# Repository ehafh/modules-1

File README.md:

Schematic and PCB files for the synthesizer modules developed by [1979](https://1979.ws/)
Open Source Buchla conversions of Mutable Instruments modules.

Currently incomplete, waiting on Grayscale / 1979 updates.

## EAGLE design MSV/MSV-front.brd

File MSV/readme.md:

Overview
=======

Modal Synthesis Voice is a synthesizer module for the Buchla format, developed and manufactured by [1979](https://1979.ws/). It is based on [Elements](https://mutable-instruments.net/modules/elements/) by [Mutable Instruments](https://mutable-instruments.net/). The original source files for Elements can be found in the Mutable Instruments [Github](https://github.com/pichenettes/eurorack) repository.

Visit [1979.ws/modal-synthesis-voice](https://1979.ws/modal-synthesis-voice/) for more information.

License
=======

These schematic and PCB files are distributed under the Creative Commons [CC-BY-SA 3.0](https://creativecommons.org/licenses/by-sa/3.0/) license, the same license used by the original hardware.

CC BY-SA 3.0 does not confer the right to use intellectual property such as trademarks, brand names, and logos. 1979, Modal Synthesis Voice, Mutable Instruments, and Elements are trademarks of their respective owners and should not be used without permission.

Firmware
=======

The MSV uses the firmware from Elements with no modifications.

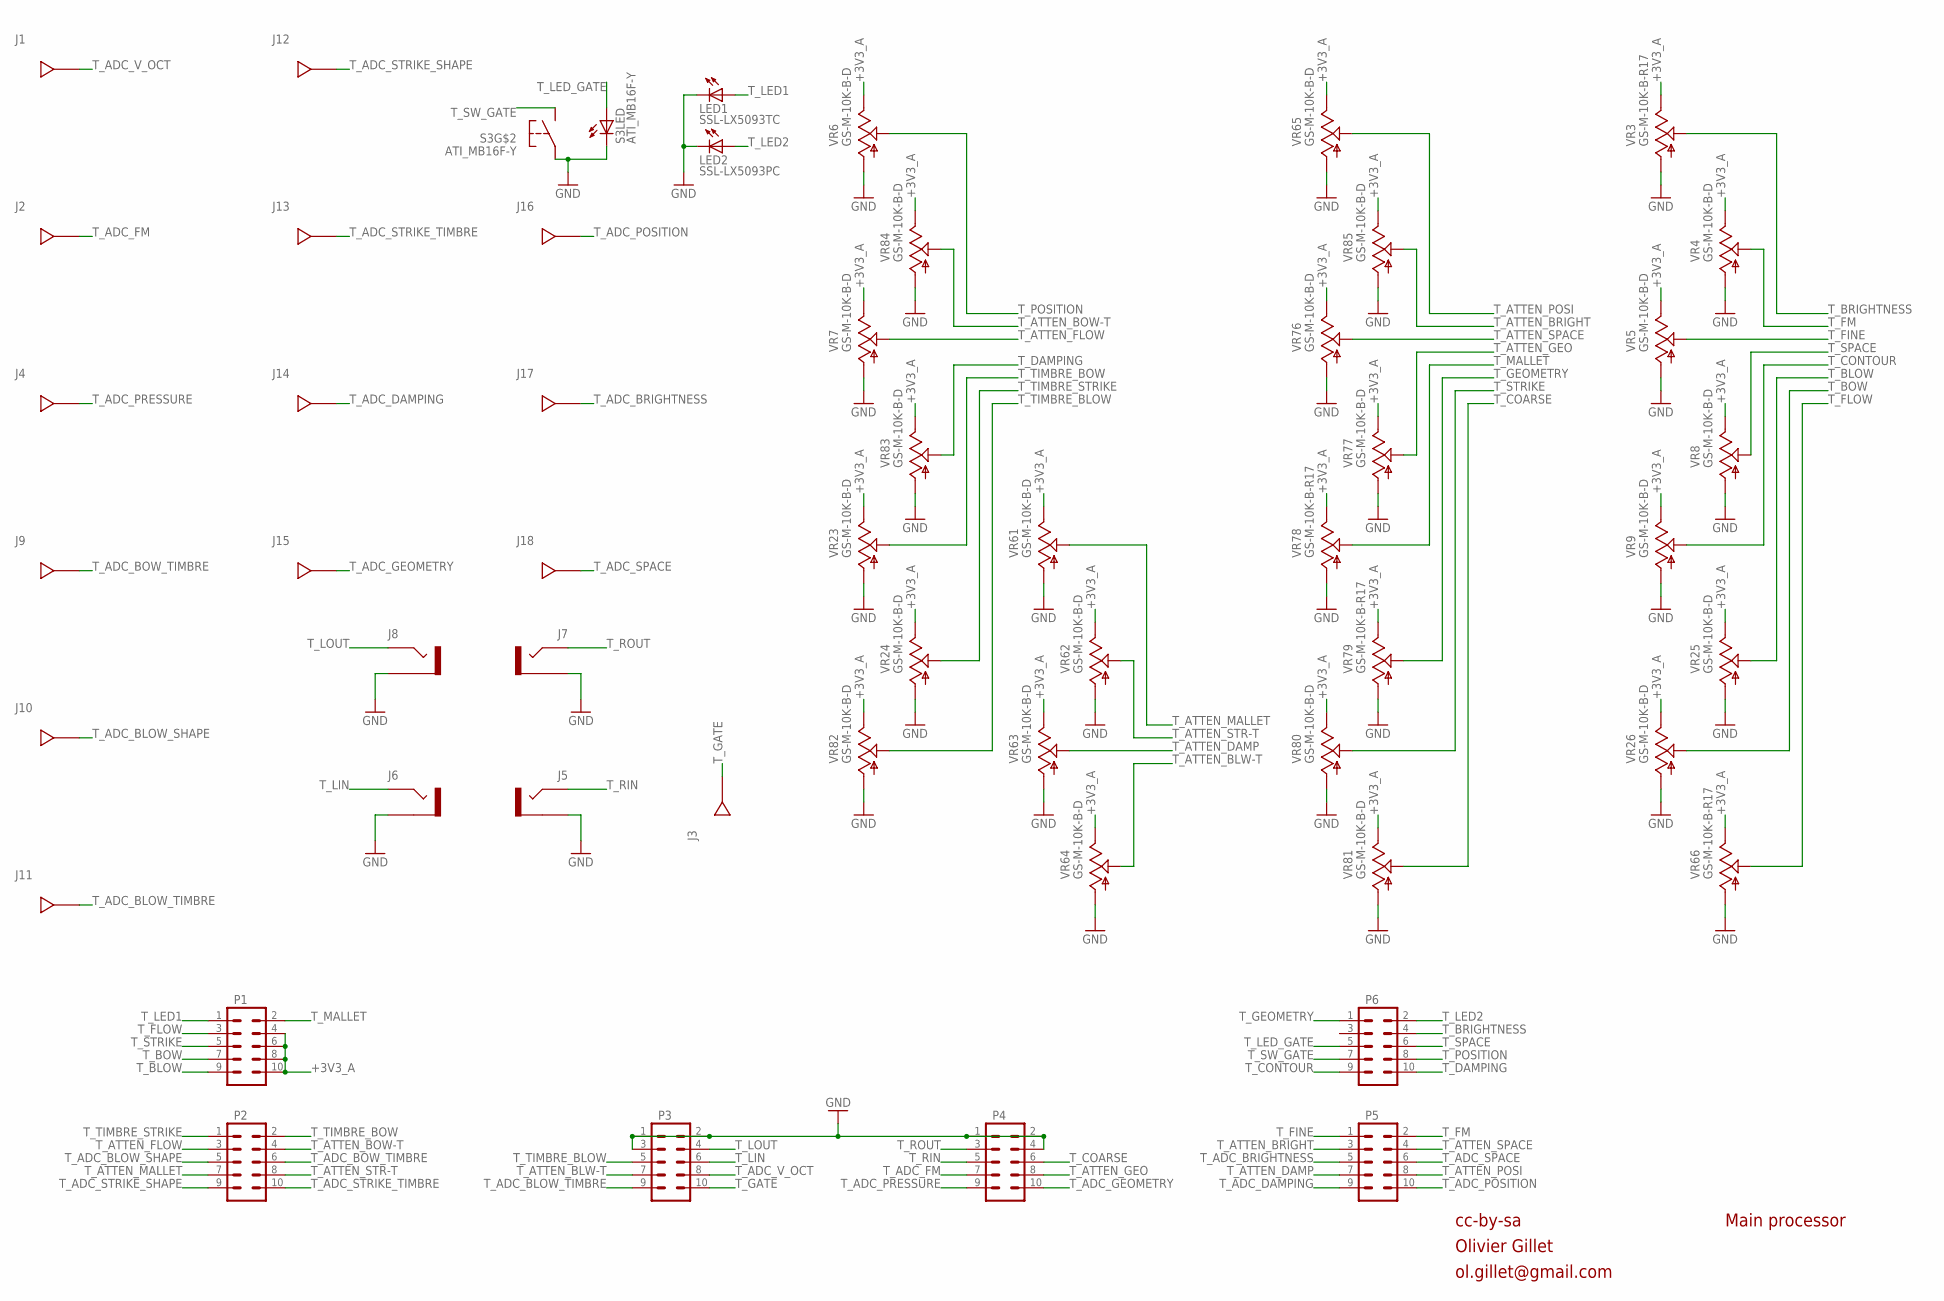
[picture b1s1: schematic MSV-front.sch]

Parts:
J1: BANANA_JACK_GRAY; JOHNSON_SILK
J2, J4, J9, J10, J11, J12, J13, J14, J15, J16, J17, J18: BANANA_JACK_BLACK; JOHNSON_SILK
J3: BANANA_JACK_ORANGE; JOHNSON_SILK
J5, J6, J7, J8: BUCHLA_AUDIO_JACK_ALT; AUDIO_ALT
LED1: SSL-LX5093TC; LED_SILK
LED2: SSL-LX5093PC; LED_SILK
P1, P2, P3, P4, P5, P6: M05X2_LOCK_FEMALE; 2X5_LOCK_FEMALE
S3: ATI_MB16F-Y; MB16F_SILK
VR3, VR66, VR78, VR79: GS-M-10K-B-R17; 9MM_SNAP-IN_POT_SILK
VR4, VR5, VR6, VR7, VR8, VR9, VR23, VR24, VR25, VR26, VR61, VR62, VR63, VR64, VR65, VR76, VR77, VR80, VR81, VR82, VR83, VR84, VR85: GS-M-10K-B-D; 9MM_SNAP-IN_POT_SILK

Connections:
+3V3_A: P1.4, P1.6, P1.8, P1.10, VR3.3, VR4.3, VR5.3, VR6.3, VR7.3, VR8.3, VR9.3, VR23.3, VR24.3, VR25.3, VR26.3, VR61.3, VR62.3, VR63.3, VR64.3, VR65.3, VR66.3, VR76.3, VR77.3, VR78.3, VR79.3, VR80.3, VR81.3, VR82.3, VR83.3, VR84.3, VR85.3
GND: J5.G (2), J6.G (2), J7.G (2), J8.G (2), LED1.K (C), LED2.K (C), P3.1, P3.2, P3.3, P4.1, P4.2, P4.4, S3.2 (1), S3.4 (L2), VR3.1, VR4.1, VR5.1, VR6.1, VR7.1, VR8.1, VR9.1, VR23.1, VR24.1, VR25.1, VR26.1, VR61.1, VR62.1, VR63.1, VR64.1, VR65.1, VR66.1, VR76.1, VR77.1, VR78.1, VR79.1, VR80.1, VR81.1, VR82.1, VR83.1, VR84.1, VR85.1
T_ADC_BLOW_SHAPE: J10.1, P2.5
T_ADC_BLOW_TIMBRE: J11.1, P3.9
T_ADC_BOW_TIMBRE: J9.1, P2.6
T_ADC_BRIGHTNESS: J17.1, P5.5
T_ADC_DAMPING: J14.1, P5.9
T_ADC_FM: J2.1, P4.7
T_ADC_GEOMETRY: J15.1, P4.10
T_ADC_POSITION: J16.1, P5.10
T_ADC_PRESSURE: J4.1, P4.9
T_ADC_SPACE: J18.1, P5.6
T_ADC_STRIKE_SHAPE: J12.1, P2.9
T_ADC_STRIKE_TIMBRE: J13.1, P2.10
T_ADC_V_OCT: J1.1, P3.8
T_ATTEN_BLW-T: P3.7, VR64.2
T_ATTEN_BOW-T: P2.4, VR84.2
T_ATTEN_BRIGHT: P5.3, VR85.2
T_ATTEN_DAMP: P5.7, VR63.2
T_ATTEN_FLOW: P2.3, VR7.2
T_ATTEN_GEO: P4.8, VR77.2
T_ATTEN_MALLET: P2.7, VR61.2
T_ATTEN_POSI: P5.8, VR65.2
T_ATTEN_SPACE: P5.4, VR76.2
T_ATTEN_STR-T: P2.8, VR62.2
T_BLOW: P1.9, VR25.2
T_BOW: P1.7, VR26.2
T_BRIGHTNESS: P6.4, VR3.2
T_COARSE: P4.6, VR81.2
T_CONTOUR: P6.9, VR9.2
T_DAMPING: P6.10, VR83.2
T_FINE: P5.1, VR5.2
T_FLOW: P1.3, VR66.2
T_FM: P5.2, VR4.2
T_GATE: J3.1, P3.10
T_GEOMETRY: P6.1, VR79.2
T_LED1: LED1.A, P1.1
T_LED2: LED2.A, P6.2
T_LED_GATE: P6.5, S3.3 (L1)
T_LIN: J6.S (1), P3.6
T_LOUT: J8.S (1), P3.4
T_MALLET: P1.2, VR78.2
T_POSITION: P6.8, VR6.2
T_RIN: J5.S (1), P4.5
T_ROUT: J7.S (1), P4.3
T_SPACE: P6.6, VR8.2
T_STRIKE: P1.5, VR80.2
T_SW_GATE: P6.7, S3.1 (2)
T_TIMBRE_BLOW: P3.5, VR82.2
T_TIMBRE_BOW: P2.2, VR23.2
T_TIMBRE_STRIKE: P2.1, VR24.2

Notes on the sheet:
cc-by-sa
Olivier Gillet
ol.gillet@gmail.com
Main processor

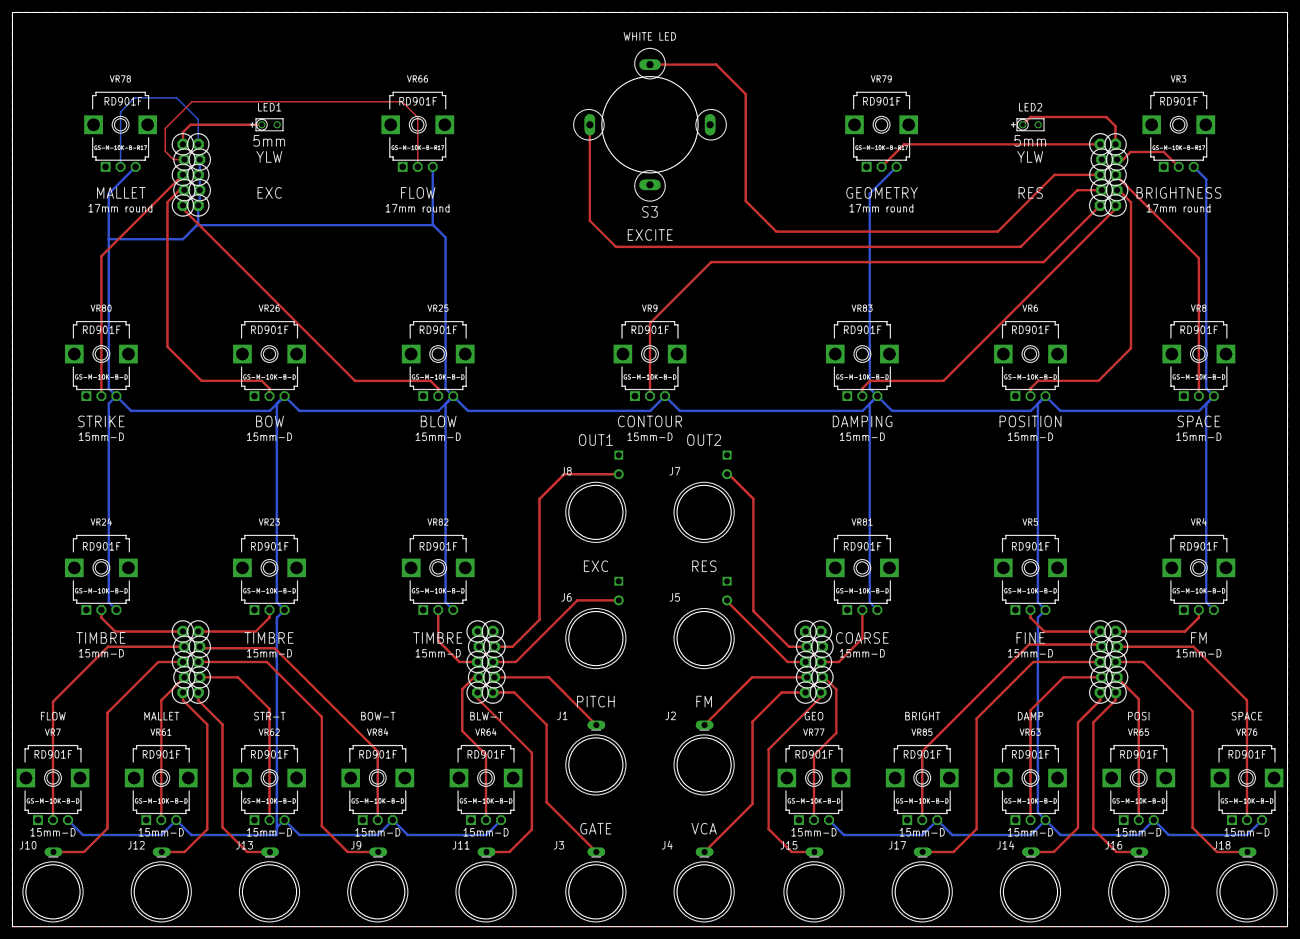
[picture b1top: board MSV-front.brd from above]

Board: 2 copper layers, 212.0 x 152.0 mm, 54 parts (1 on the bottom side), 51 nets.

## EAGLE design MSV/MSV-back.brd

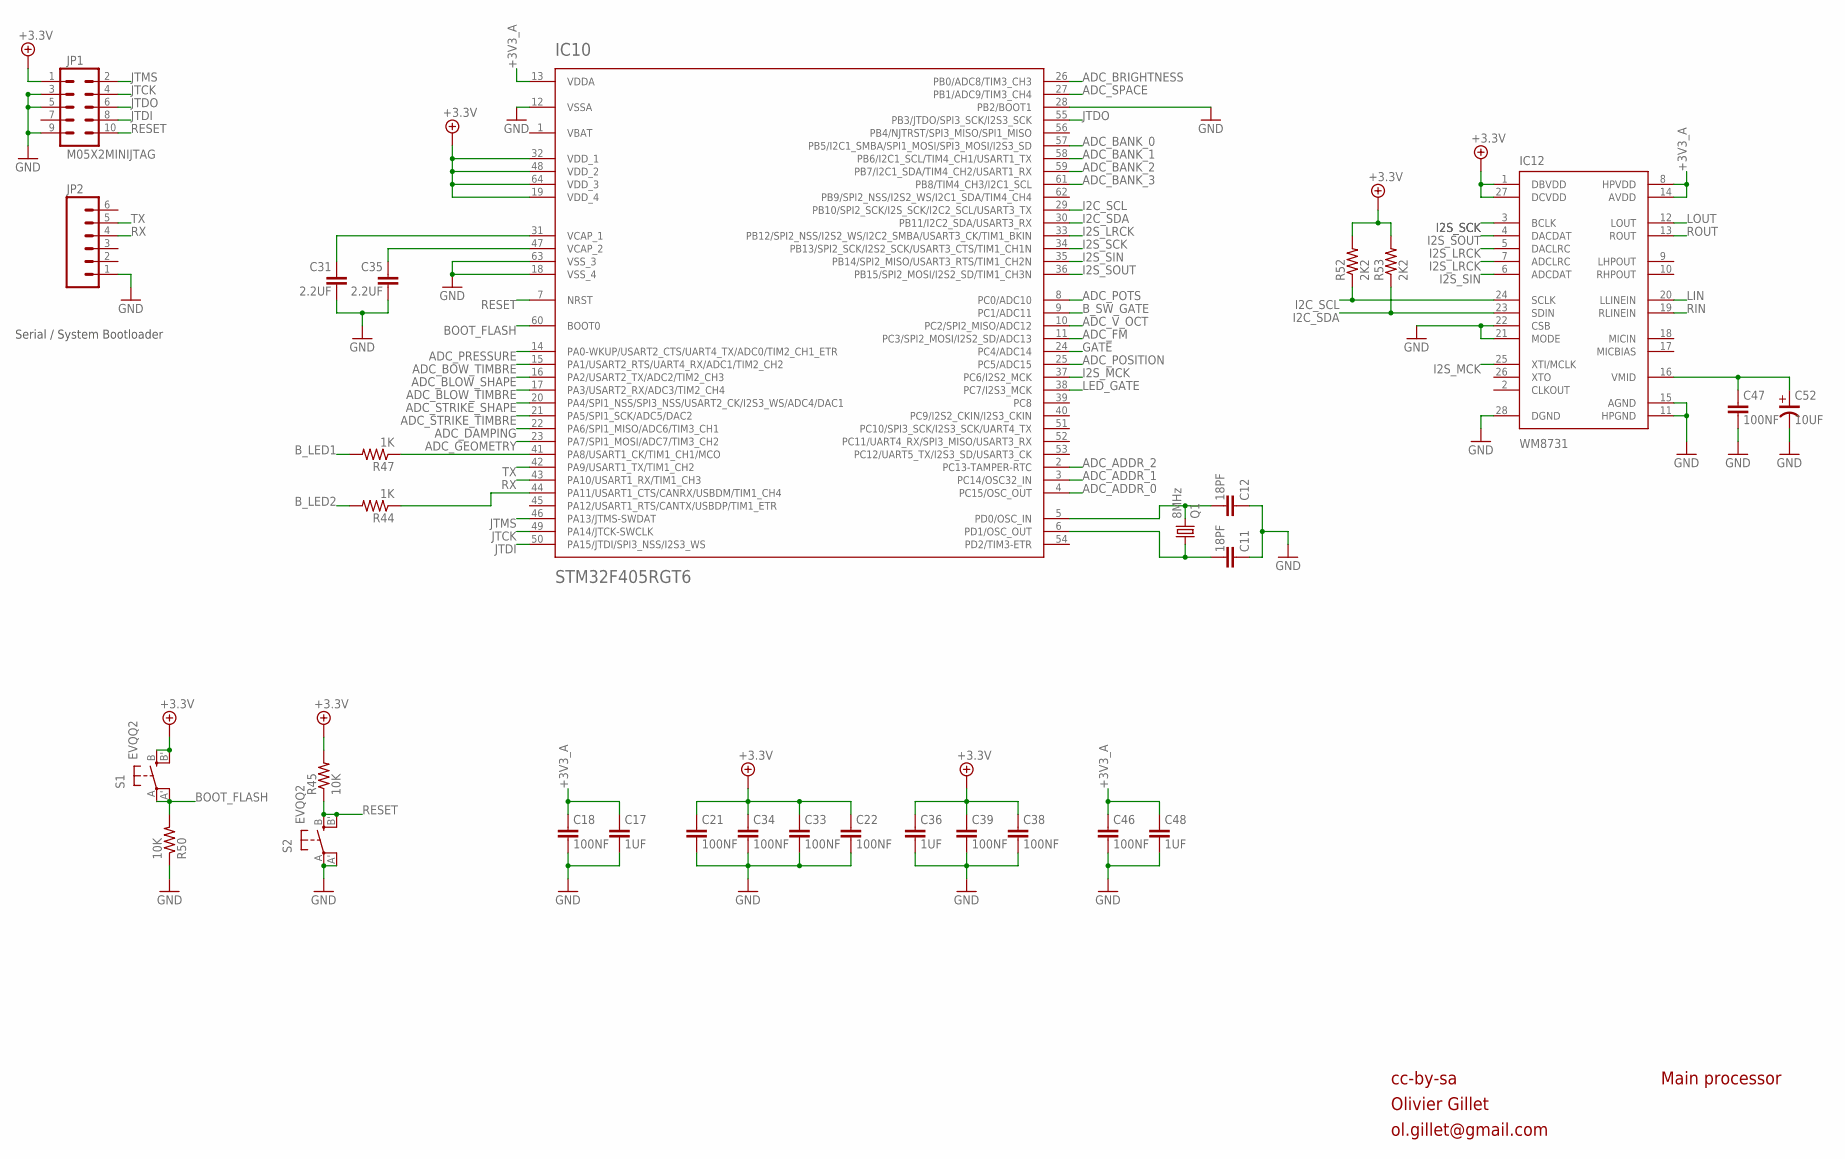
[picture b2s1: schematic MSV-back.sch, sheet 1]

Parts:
C11, C12: 18PF; C0603
C17, C36, C48: 1UF; C0603
C18, C21, C22, C33, C34, C38, C39, C46, C47: 100NF; C0603
C31, C35: 2.2UF; C0603
C52: 10UF; PANASONIC_B
IC10: STM32F405RGT6; TQFP-10X10-64
IC12: WM8731; SSOP-28
JP1: M05X2MINIJTAG; 2X5-1.27
JP2: M06_SQUARE; 1X06_SQUARE
Q1: 8MHz; HC49UP
R44, R47: 1K; R0603
R45, R50: 10K; R0603
R52, R53: 2K2; R0603
S1, S2: EVQQ2; EVQ-Q2

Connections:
+3V3_A: C17.1, C18.1, C46.1, C48.1, IC10.13 (VDDA), IC12.8 (HPVDD), IC12.14 (AVDD); also elsewhere on the board
+3V3_D: C21.1, C22.1, C33.1, C34.1, C36.1, C38.1, C39.1, IC10.19 (VDD_4), IC10.32 (VDD_1), IC10.48 (VDD_2), IC10.64 (VDD_3), IC12.1 (DBVDD), IC12.27 (DCVDD), JP1.1, R45.2, R52.2, R53.2, S1.B (S), S1.B' (S1); also elsewhere on the board
ADC_ADDR_0: IC10.4 (PC15/OSC_OUT); also elsewhere on the board
ADC_ADDR_1: IC10.3 (PC14/OSC32_IN); also elsewhere on the board
ADC_ADDR_2: IC10.2 (PC13-TAMPER-RTC); also elsewhere on the board
ADC_BANK_0: IC10.57 (PB5/I2C1_SMBA/SPI1_MOSI/SPI3_MOSI/I2S3_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); also elsewhere on the board
ADC_BANK_1: IC10.58 (PB6/I2C1_SCL/TIM4_CH1/USART1_TX); also elsewhere on the board
ADC_BANK_2: IC10.59 (PB7/I2C1_SDA/TIM4_CH2/USART1_RX); also elsewhere on the board
ADC_BANK_3: IC10.61 (PB8/TIM4_CH3/I2C1_SCL); also elsewhere on the board
ADC_BLOW_SHAPE: IC10.16 (PA2/USART2_TX/ADC2/TIM2_CH3); also elsewhere on the board
ADC_BLOW_TIMBRE: IC10.17 (PA3/USART2_RX/ADC3/TIM2_CH4); also elsewhere on the board
ADC_BOW_TIMBRE: IC10.15 (PA1/USART2_RTS/UART4_RX/ADC1/TIM2_CH2); also elsewhere on the board
ADC_BRIGHTNESS: IC10.26 (PB0/ADC8/TIM3_CH3); also elsewhere on the board
ADC_DAMPING: IC10.22 (PA6/SPI1_MISO/ADC6/TIM3_CH1); also elsewhere on the board
ADC_FM: IC10.11 (PC3/SPI2_MOSI/I2S2_SD/ADC13); also elsewhere on the board
ADC_GEOMETRY: IC10.23 (PA7/SPI1_MOSI/ADC7/TIM3_CH2); also elsewhere on the board
ADC_POSITION: IC10.25 (PC5/ADC15); also elsewhere on the board
ADC_POTS: IC10.8 (PC0/ADC10); also elsewhere on the board
ADC_PRESSURE: IC10.14 (PA0-WKUP/USART2_CTS/UART4_TX/ADC0/TIM2_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); also elsewhere on the board
ADC_SPACE: IC10.27 (PB1/ADC9/TIM3_CH4); also elsewhere on the board
ADC_STRIKE_SHAPE: IC10.20 (PA4/SPI1_NSS/SPI3_NSS/USART2_CK/I2S3_WS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); also elsewhere on the board
ADC_STRIKE_TIMBRE: IC10.21 (PA5/SPI1_SCK/ADC5/DAC2); also elsewhere on the board
ADC_V_OCT: IC10.10 (PC2/SPI2_MISO/ADC12); also elsewhere on the board
BOOT_FLASH: IC10.60 (BOOT0), R50.2, S1.A, S1.A' (P1)
B_LED1: R47.2; also elsewhere on the board
B_LED2: R44.2; also elsewhere on the board
B_SW_GATE: IC10.9 (PC1/ADC11); also elsewhere on the board
GATE: IC10.24 (PC4/ADC14); also elsewhere on the board
GND: C11.1, C12.1, C17.2, C18.2, C21.2, C22.2, C31.2, C33.2, C34.2, C35.2, C36.2, C38.2, C39.2, C46.2, C47.2, C48.2, C52.- (NEG), IC10.12 (VSSA), IC10.18 (VSS_4), IC10.28 (PB2/BOOT1), IC10.63 (VSS_3), IC12.11 (HPGND), IC12.15 (AGND), IC12.21 (MODE), IC12.22 (CSB), IC12.28 (DGND), JP1.3, JP1.5, JP1.9, JP2.1, R50.1, S2.A, S2.A' (P1); also elsewhere on the board
I2C_SCL: IC10.29 (PB10/SPI2_SCK/I2S_SCK/I2C2_SCL/USART3_TX), IC12.24 (SCLK), R52.1
I2C_SDA: IC10.30 (PB11/I2C2_SDA/USART3_RX), IC12.23 (SDIN), R53.1
I2S_LRCK: IC10.33 (PB12/SPI2_NSS/I2S2_WS/I2C2_SMBA/USART3_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), IC12.5 (DACLRC), IC12.7 (ADCLRC)
I2S_MCK: IC10.37 (PC6/I2S2_MCK), IC12.25 (XTI/MCLK)
I2S_SCK: IC10.34 (PB13/SPI2_SCK/I2S2_SCK/USART3_CTS/TIM1_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), IC12.3 (BCLK)
I2S_SIN: IC10.35 (PB14/SPI2_MISO/USART3_RTS/TIM1_CH2N), IC12.6 (ADCDAT)
I2S_SOUT: IC10.36 (PB15/SPI2_MOSI/I2S2_SD/TIM1_CH3N), IC12.4 (DACDAT)
JTCK: IC10.49 (PA14/JTCK-SWCLK), JP1.4
JTDI: IC10.50 (PA15/JTDI/SPI3_NSS/I2S3_WS), JP1.8
JTDO: IC10.55 (PB3/JTDO/SPI3_SCK/I2S3_SCK), JP1.6
JTMS: IC10.46 (PA13/JTMS-SWDAT), JP1.2
LED_GATE: IC10.38 (PC7/I2S3_MCK); also elsewhere on the board
LIN: IC12.20 (LLINEIN); also elsewhere on the board
LOUT: IC12.12 (LOUT); also elsewhere on the board
unnamed: C12.2, IC10.5 (PD0/OSC_IN), Q1.2
unnamed: C11.2, IC10.6 (PD1/OSC_OUT), Q1.1
unnamed: C35.1, IC10.47 (VCAP_2)
unnamed: C47.1, C52.+ (POS), IC12.16 (VMID)
unnamed: C31.1, IC10.31 (VCAP_1)
unnamed: IC10.44 (PA11/USART1_CTS/CANRX/USBDM/TIM1_CH4), R44.1
unnamed: IC10.41 (PA8/USART1_CK/TIM1_CH1/MCO), R47.1
RESET: IC10.7 (NRST), JP1.10, R45.1, S2.B (S), S2.B' (S1)
RIN: IC12.19 (RLINEIN); also elsewhere on the board
ROUT: IC12.13 (ROUT); also elsewhere on the board
RX: IC10.43 (PA10/USART1_RX/TIM1_CH3), JP2.4
TX: IC10.42 (PA9/USART1_TX/TIM1_CH2), JP2.5
VBAT: IC10.1 (VBAT)

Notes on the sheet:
cc-by-sa
Olivier Gillet
ol.gillet@gmail.com
Main processor
Serial / System Bootloader

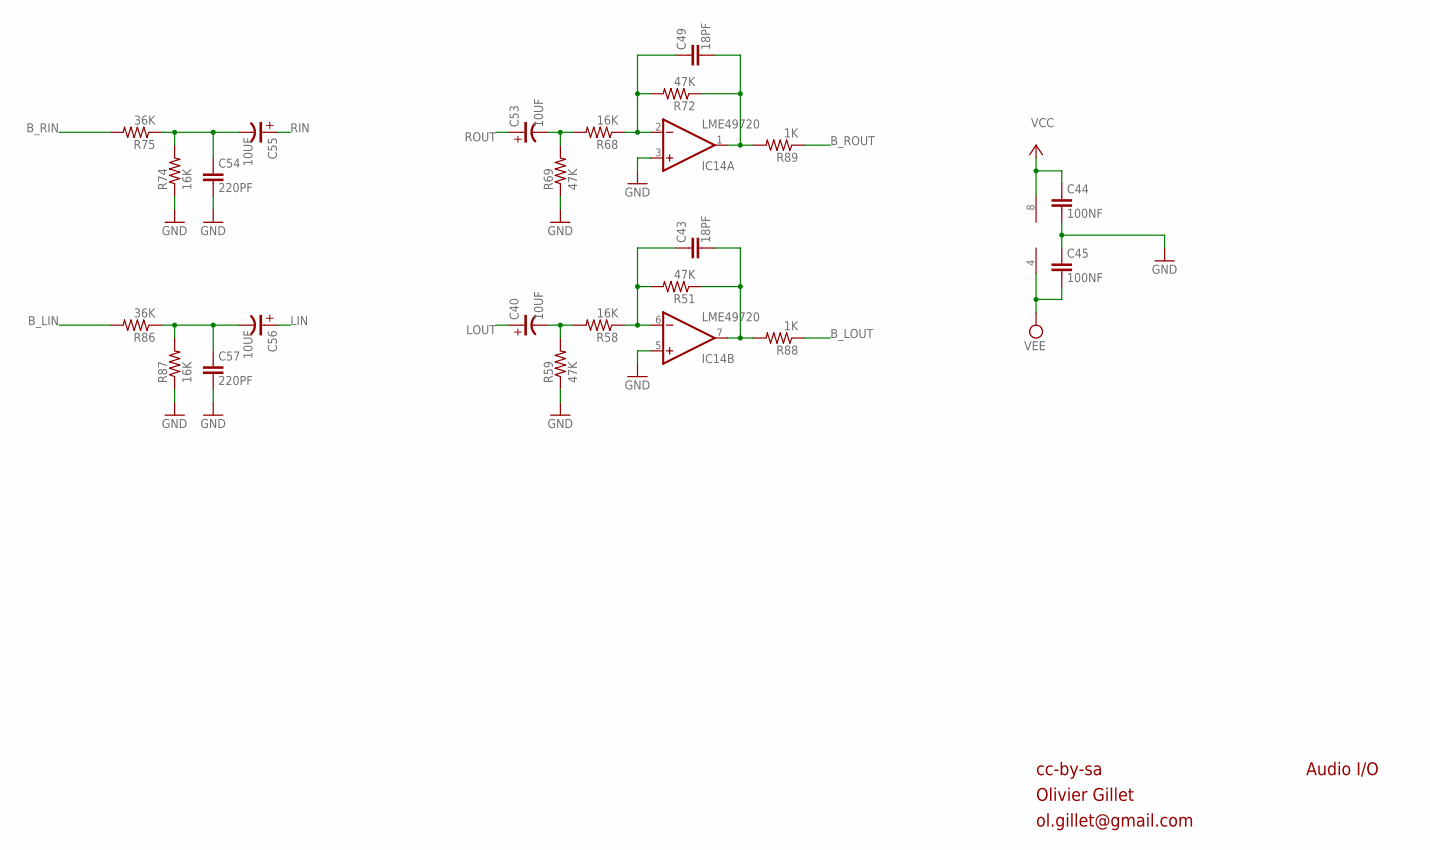
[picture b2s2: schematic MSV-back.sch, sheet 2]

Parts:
C40, C53, C55, C56: 10UF; PANASONIC_B
C43, C49: 18PF; C0603
C44, C45: 100NF; C0603
C54, C57: 220PF; C0603
IC14: LME49720; TSSOP-8
R51, R59, R69, R72: 47K; R0603
R58, R68, R74, R87: 16K; R0603
R75, R86: 36K; R0603
R88, R89: 1K; R0603

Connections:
B_LIN: R86.2; also elsewhere on the board
B_LOUT: R88.1; also elsewhere on the board
B_RIN: R75.2; also elsewhere on the board
B_ROUT: R89.1; also elsewhere on the board
GND: C44.2, C45.1, C54.2, C57.2, IC14.3 (+IN), IC14.5 (+IN), R59.1, R69.1, R74.1, R87.1; also elsewhere on the board
LIN: C56.+ (POS); also elsewhere on the board
LOUT: C40.+ (POS); also elsewhere on the board
unnamed: C56.- (NEG), C57.1, R86.1, R87.2
unnamed: C54.1, C55.- (NEG), R74.2, R75.1
unnamed: C40.- (NEG), R58.2, R59.2
unnamed: C43.1, IC14.6 (-IN), R51.2, R58.1
unnamed: C43.2, IC14.7 (OUT), R51.1, R88.2
unnamed: C53.- (NEG), R68.2, R69.2
unnamed: C49.1, IC14.2 (-IN), R68.1, R72.2
unnamed: C49.2, IC14.1 (OUT), R72.1, R89.2
RIN: C55.+ (POS); also elsewhere on the board
ROUT: C53.+ (POS); also elsewhere on the board
VCC: C44.1, IC14.8 (V+); also elsewhere on the board
VEE: C45.2, IC14.4 (V-); also elsewhere on the board

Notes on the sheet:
cc-by-sa
Olivier Gillet
ol.gillet@gmail.com
Audio I/O

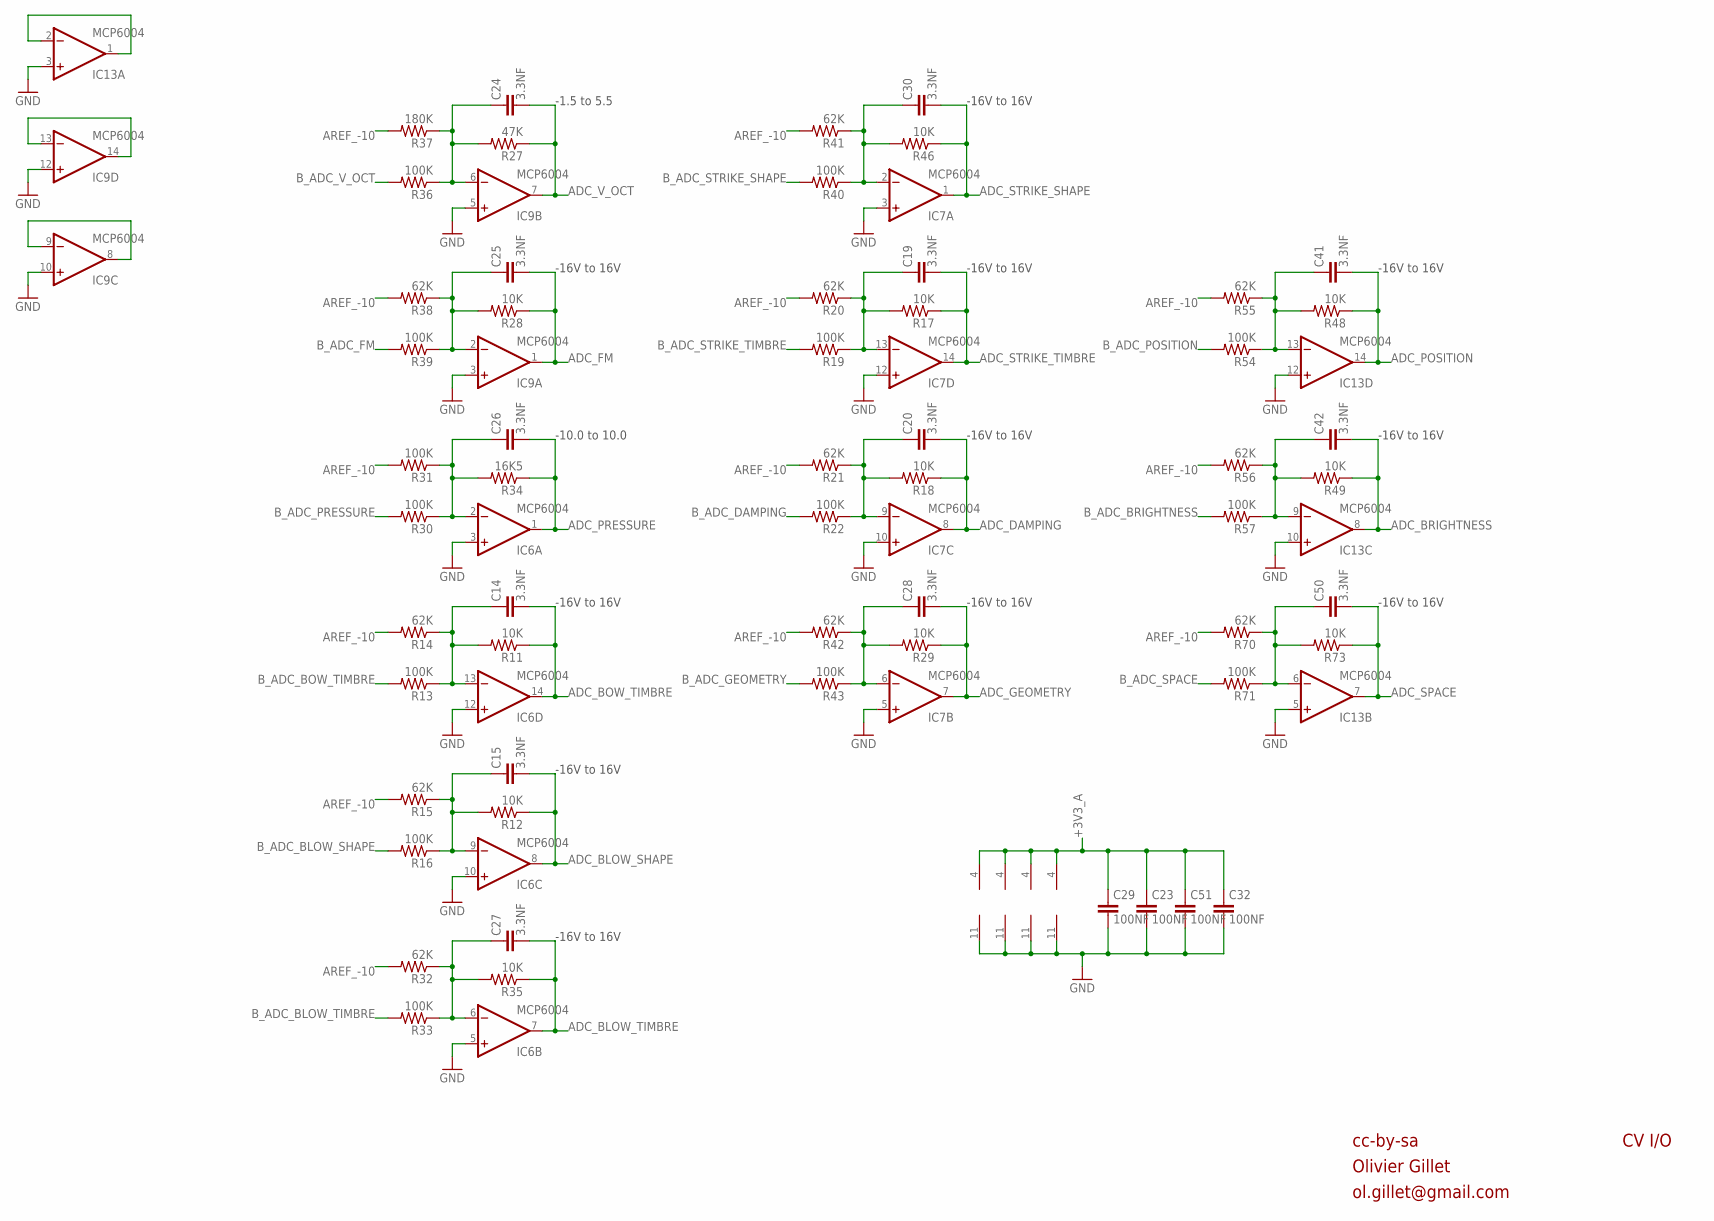
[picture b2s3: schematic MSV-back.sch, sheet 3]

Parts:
C14, C15, C19, C20, C24, C25, C26, C27, C28, C30, C41, C42, C50: 3.3NF; C0603
C23, C29, C32, C51: 100NF; C0603
IC6, IC7, IC9, IC13: MCP6004; TSSOP-14
R11, R12, R17, R18, R28, R29, R35, R46, R48, R49, R73: 10K; R0603
R13, R16, R19, R22, R30, R31, R33, R36, R39, R40, R43, R54, R57, R71: 100K; R0603
R14, R15, R20, R21, R32, R38, R41, R42, R55, R56, R70: 62K; R0603
R27: 47K; R0603
R34: 16K5; R0603
R37: 180K; R0603

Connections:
+3V3_A: C23.1, C29.1, C32.1, C51.1, IC6.4 (V+), IC7.4 (V+), IC9.4 (V+), IC13.4 (V+); also elsewhere on the board
ADC_BLOW_SHAPE: C15.2, IC6.8 (OUT), R12.1; also elsewhere on the board
ADC_BLOW_TIMBRE: C27.2, IC6.7 (OUT), R35.1; also elsewhere on the board
ADC_BOW_TIMBRE: C14.2, IC6.14 (OUT), R11.1; also elsewhere on the board
ADC_BRIGHTNESS: C42.2, IC13.8 (OUT), R49.1; also elsewhere on the board
ADC_DAMPING: C20.2, IC7.8 (OUT), R18.1; also elsewhere on the board
ADC_FM: C25.2, IC9.1 (OUT), R28.1; also elsewhere on the board
ADC_GEOMETRY: C28.2, IC7.7 (OUT), R29.1; also elsewhere on the board
ADC_POSITION: C41.2, IC13.14 (OUT), R48.1; also elsewhere on the board
ADC_PRESSURE: C26.2, IC6.1 (OUT), R34.1; also elsewhere on the board
ADC_SPACE: C50.2, IC13.7 (OUT), R73.1; also elsewhere on the board
ADC_STRIKE_SHAPE: C30.2, IC7.1 (OUT), R46.1; also elsewhere on the board
ADC_STRIKE_TIMBRE: C19.2, IC7.14 (OUT), R17.1; also elsewhere on the board
ADC_V_OCT: C24.2, IC9.7 (OUT), R27.1; also elsewhere on the board
AREF_-10: R14.2, R15.2, R20.2, R21.2, R31.2, R32.2, R37.2, R38.2, R41.2, R42.2, R55.2, R56.2, R70.2; also elsewhere on the board
B_ADC_BLOW_SHAPE: R16.2; also elsewhere on the board
B_ADC_BLOW_TIMBRE: R33.2; also elsewhere on the board
B_ADC_BOW_TIMBRE: R13.2; also elsewhere on the board
B_ADC_BRIGHTNESS: R57.2; also elsewhere on the board
B_ADC_DAMPING: R22.2; also elsewhere on the board
B_ADC_FM: R39.2; also elsewhere on the board
B_ADC_GEOMETRY: R43.2; also elsewhere on the board
B_ADC_POSITION: R54.2; also elsewhere on the board
B_ADC_PRESSURE: R30.2; also elsewhere on the board
B_ADC_SPACE: R71.2; also elsewhere on the board
B_ADC_STRIKE_SHAPE: R40.2; also elsewhere on the board
B_ADC_STRIKE_TIMBRE: R19.2; also elsewhere on the board
B_ADC_V_OCT: R36.2; also elsewhere on the board
GND: C23.2, C29.2, C32.2, C51.2, IC6.3 (+IN), IC6.5 (+IN), IC6.10 (+IN), IC6.11 (V-), IC6.12 (+IN), IC7.3 (+IN), IC7.5 (+IN), IC7.10 (+IN), IC7.11 (V-), IC7.12 (+IN), IC9.3 (+IN), IC9.5 (+IN), IC9.10 (+IN), IC9.11 (V-), IC9.12 (+IN), IC13.3 (+IN), IC13.5 (+IN), IC13.10 (+IN), IC13.11 (V-), IC13.12 (+IN); also elsewhere on the board
unnamed: C15.1, IC6.9 (-IN), R12.2, R15.1, R16.1
unnamed: C14.1, IC6.13 (-IN), R11.2, R13.1, R14.1
unnamed: C19.1, IC7.13 (-IN), R17.2, R19.1, R20.1
unnamed: C24.1, IC9.6 (-IN), R27.2, R36.1, R37.1
unnamed: C20.1, IC7.9 (-IN), R18.2, R21.1, R22.1
unnamed: C25.1, IC9.2 (-IN), R28.2, R38.1, R39.1
unnamed: C30.1, IC7.2 (-IN), R40.1, R41.1, R46.2
unnamed: C27.1, IC6.6 (-IN), R32.1, R33.1, R35.2
unnamed: C42.1, IC13.9 (-IN), R49.2, R56.1, R57.1
unnamed: C50.1, IC13.6 (-IN), R70.1, R71.1, R73.2
unnamed: C28.1, IC7.6 (-IN), R29.2, R42.1, R43.1
unnamed: C41.1, IC13.13 (-IN), R48.2, R54.1, R55.1
unnamed: C26.1, IC6.2 (-IN), R30.1, R31.1, R34.2
unnamed: IC13.1 (OUT), IC13.2 (-IN)
unnamed: IC9.13 (-IN), IC9.14 (OUT)
unnamed: IC9.8 (OUT), IC9.9 (-IN)

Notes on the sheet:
cc-by-sa
Olivier Gillet
ol.gillet@gmail.com
CV I/O
-1.5 to 5.5
-16V to 16V
-10.0 to 10.0

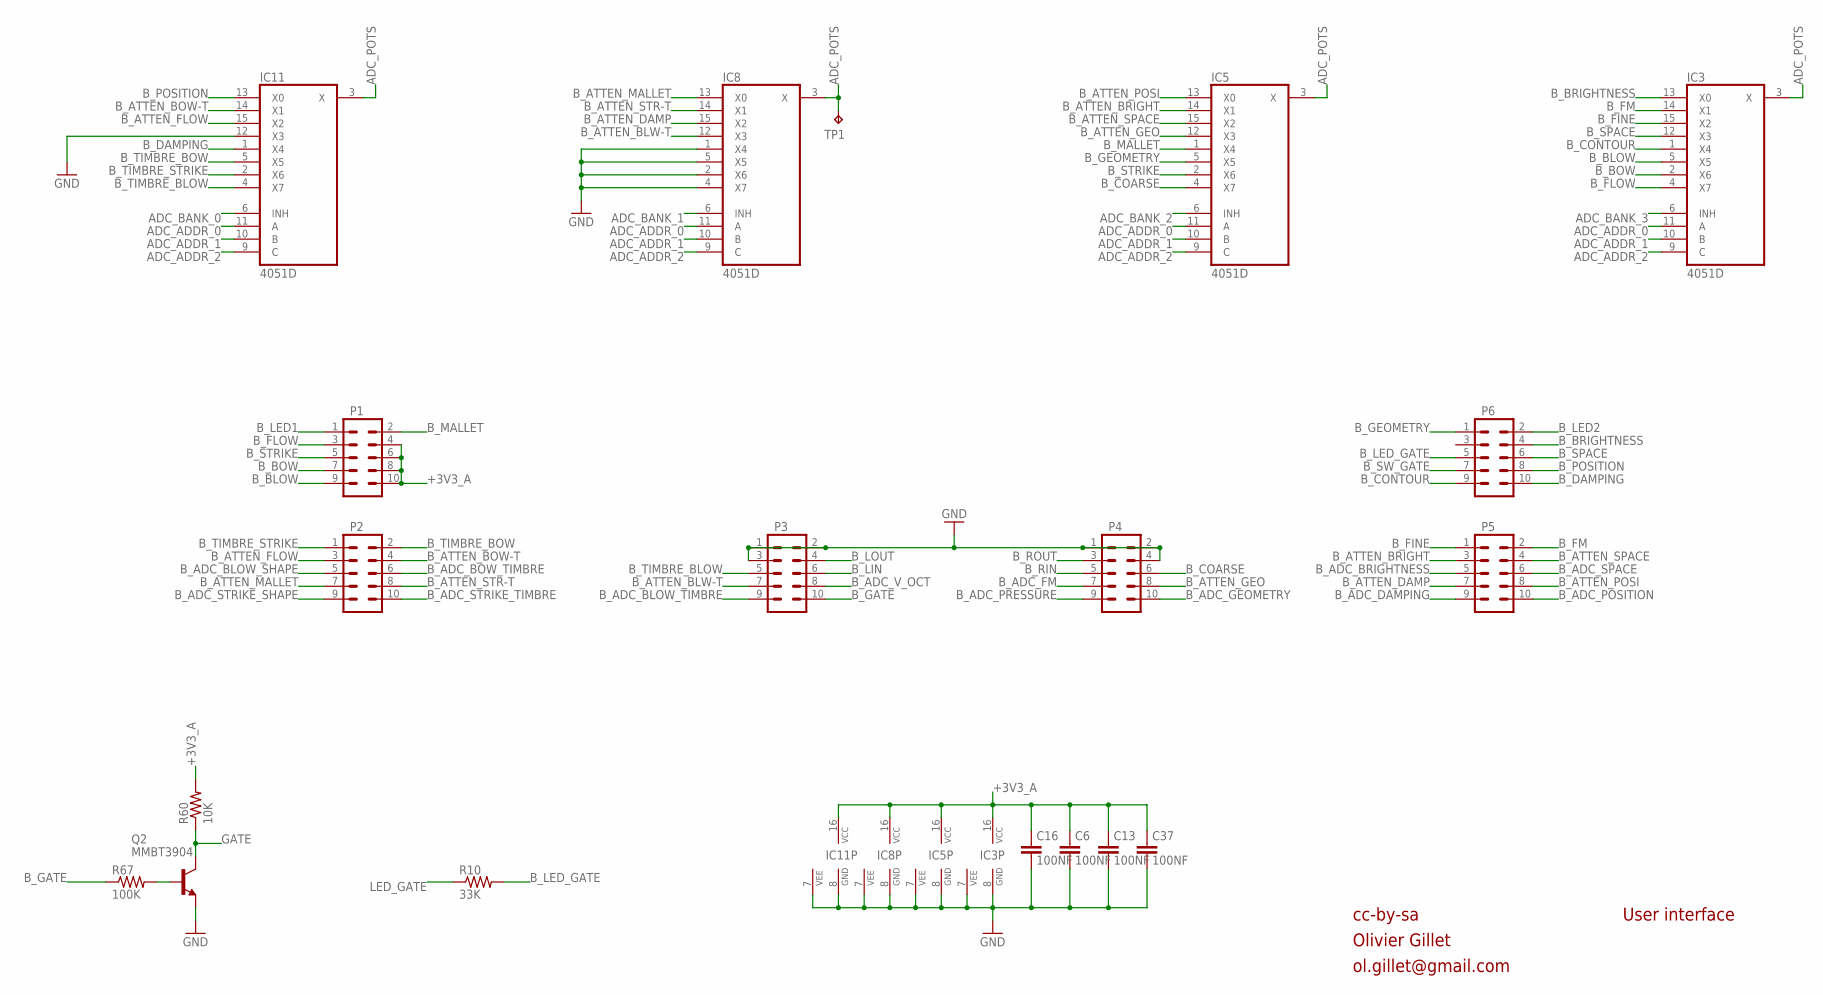
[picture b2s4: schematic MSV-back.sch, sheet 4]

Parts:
C6, C13, C16, C37: 100NF; C0603
IC3, IC5, IC8, IC11: 4051D; SO-16
P1, P2, P3, P4, P5, P6: M05X2_LOCK_MALE; 2X5_LOCK_MALE
Q2: MMBT3904; SOT23-BEC
R10: 33K; R0603
R60: 10K; R0603
R67: 100K; R0603
TP1: TPTP15R; TP15R

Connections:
+3V3_A: C6.1, C13.1, C16.1, C37.1, IC3.16 (VCC), IC5.16 (VCC), IC8.16 (VCC), IC11.16 (VCC), P1.4, P1.6, P1.8, P1.10, R60.2; also elsewhere on the board
ADC_ADDR_0: IC3.11 (A), IC5.11 (A), IC8.11 (A), IC11.11 (A); also elsewhere on the board
ADC_ADDR_1: IC3.10 (B), IC5.10 (B), IC8.10 (B), IC11.10 (B); also elsewhere on the board
ADC_ADDR_2: IC3.9 (C), IC5.9 (C), IC8.9 (C), IC11.9 (C); also elsewhere on the board
ADC_BANK_0: IC11.6 (INH); also elsewhere on the board
ADC_BANK_1: IC8.6 (INH); also elsewhere on the board
ADC_BANK_2: IC5.6 (INH); also elsewhere on the board
ADC_BANK_3: IC3.6 (INH); also elsewhere on the board
ADC_POTS: IC3.3 (X), IC5.3 (X), IC8.3 (X), IC11.3 (X), TP1.TP; also elsewhere on the board
B_ADC_BLOW_SHAPE: P2.5; also elsewhere on the board
B_ADC_BLOW_TIMBRE: P3.9; also elsewhere on the board
B_ADC_BOW_TIMBRE: P2.6; also elsewhere on the board
B_ADC_BRIGHTNESS: P5.5; also elsewhere on the board
B_ADC_DAMPING: P5.9; also elsewhere on the board
B_ADC_FM: P4.7; also elsewhere on the board
B_ADC_GEOMETRY: P4.10; also elsewhere on the board
B_ADC_POSITION: P5.10; also elsewhere on the board
B_ADC_PRESSURE: P4.9; also elsewhere on the board
B_ADC_SPACE: P5.6; also elsewhere on the board
B_ADC_STRIKE_SHAPE: P2.9; also elsewhere on the board
B_ADC_STRIKE_TIMBRE: P2.10; also elsewhere on the board
B_ADC_V_OCT: P3.8; also elsewhere on the board
B_ATTEN_BLW-T: IC8.12 (X3), P3.7
B_ATTEN_BOW-T: IC11.14 (X1), P2.4
B_ATTEN_BRIGHT: IC5.14 (X1), P5.3
B_ATTEN_DAMP: IC8.15 (X2), P5.7
B_ATTEN_FLOW: IC11.15 (X2), P2.3
B_ATTEN_GEO: IC5.12 (X3), P4.8
B_ATTEN_MALLET: IC8.13 (X0), P2.7
B_ATTEN_POSI: IC5.13 (X0), P5.8
B_ATTEN_SPACE: IC5.15 (X2), P5.4
B_ATTEN_STR-T: IC8.14 (X1), P2.8
B_BLOW: IC3.5 (X5), P1.9
B_BOW: IC3.2 (X6), P1.7
B_BRIGHTNESS: IC3.13 (X0), P6.4
B_COARSE: IC5.4 (X7), P4.6
B_CONTOUR: IC3.1 (X4), P6.9
B_DAMPING: IC11.1 (X4), P6.10
B_FINE: IC3.15 (X2), P5.1
B_FLOW: IC3.4 (X7), P1.3
B_FM: IC3.14 (X1), P5.2
B_GATE: P3.10, R67.1
B_GEOMETRY: IC5.5 (X5), P6.1
B_LED1: P1.1; also elsewhere on the board
B_LED2: P6.2; also elsewhere on the board
B_LED_GATE: P6.5, R10.2
B_LIN: P3.6; also elsewhere on the board
B_LOUT: P3.4; also elsewhere on the board
B_MALLET: IC5.1 (X4), P1.2
B_POSITION: IC11.13 (X0), P6.8
B_RIN: P4.5; also elsewhere on the board
B_ROUT: P4.3; also elsewhere on the board
B_SPACE: IC3.12 (X3), P6.6
B_STRIKE: IC5.2 (X6), P1.5
B_SW_GATE: P6.7; also elsewhere on the board
B_TIMBRE_BLOW: IC11.4 (X7), P3.5
B_TIMBRE_BOW: IC11.5 (X5), P2.2
B_TIMBRE_STRIKE: IC11.2 (X6), P2.1
GATE: Q2.C, R60.1; also elsewhere on the board
GND: C6.2, C13.2, C16.2, C37.2, IC3.7 (VEE), IC3.8 (GND), IC5.7 (VEE), IC5.8 (GND), IC8.1 (X4), IC8.2 (X6), IC8.4 (X7), IC8.5 (X5), IC8.7 (VEE), IC8.8 (GND), IC11.7 (VEE), IC11.8 (GND), IC11.12 (X3), P3.1, P3.2, P3.3, P4.1, P4.2, P4.4, Q2.E; also elsewhere on the board
LED_GATE: R10.1; also elsewhere on the board
unnamed: Q2.B, R67.2

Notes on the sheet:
cc-by-sa
Olivier Gillet
ol.gillet@gmail.com
User interface

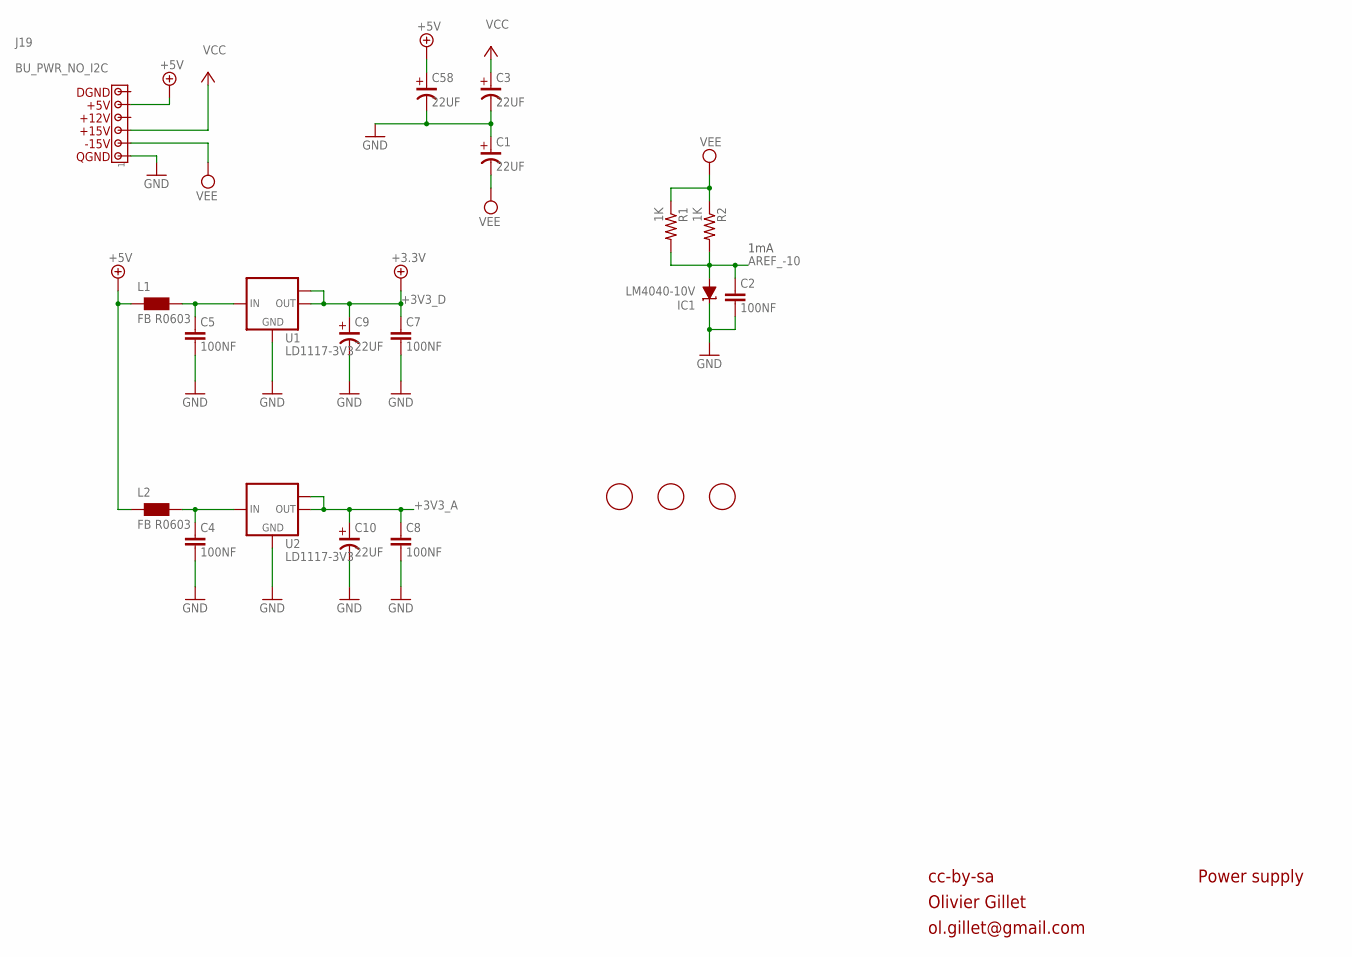
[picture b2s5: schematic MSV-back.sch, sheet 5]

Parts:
C1, C3, C9, C10, C58: 22UF; PANASONIC_C
C2, C4, C5, C7, C8: 100NF; C0603
FD1, FD2, FD3: FIDUCIAL; FIDUCIAL_1MM
IC1: LM4040-10V; DBZ_R-PDSO-G3
J19: BU_PWR_NO_I2C; MTA_156
L1, L2: FB R0603; WUERTH-ELEKTRONIK_0603
R1, R2: 1K; R0603
U1, U2: LD1117-3V3; SOT223

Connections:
+3V3_A: C8.1, C10.+ (POS), U2.2 (OUT), U2.TAB (OUT1); also elsewhere on the board
+3V3_D: C7.1, C9.+ (POS), U1.2 (OUT), U1.TAB (OUT1); also elsewhere on the board
+5V: C58.+ (POS), J19.5, L1.1, L2.1
AREF_-10: C2.1, IC1.2 (A), R1.2, R2.2; also elsewhere on the board
GND: C1.+ (POS), C2.2, C3.- (NEG), C4.2, C5.2, C7.2, C8.2, C9.- (NEG), C10.- (NEG), C58.- (NEG), IC1.1 (C), J19.1, U1.1 (GND), U2.1 (GND); also elsewhere on the board
unnamed: C5.1, L1.2, U1.3 (IN)
unnamed: C4.1, L2.2, U2.3 (IN)
VCC: C3.+ (POS), J19.3; also elsewhere on the board
VEE: C1.- (NEG), J19.2, R1.1, R2.1; also elsewhere on the board

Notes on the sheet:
1mA
cc-by-sa
Olivier Gillet
ol.gillet@gmail.com
Power supply

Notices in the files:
DR/DR.brd:
Original hardware and code:
E. Gillet CC-BY-SA 3.0
SMP/SMP.brd:
Original hardware and code by Olivier Gillet CC-BY-SA-3.0
